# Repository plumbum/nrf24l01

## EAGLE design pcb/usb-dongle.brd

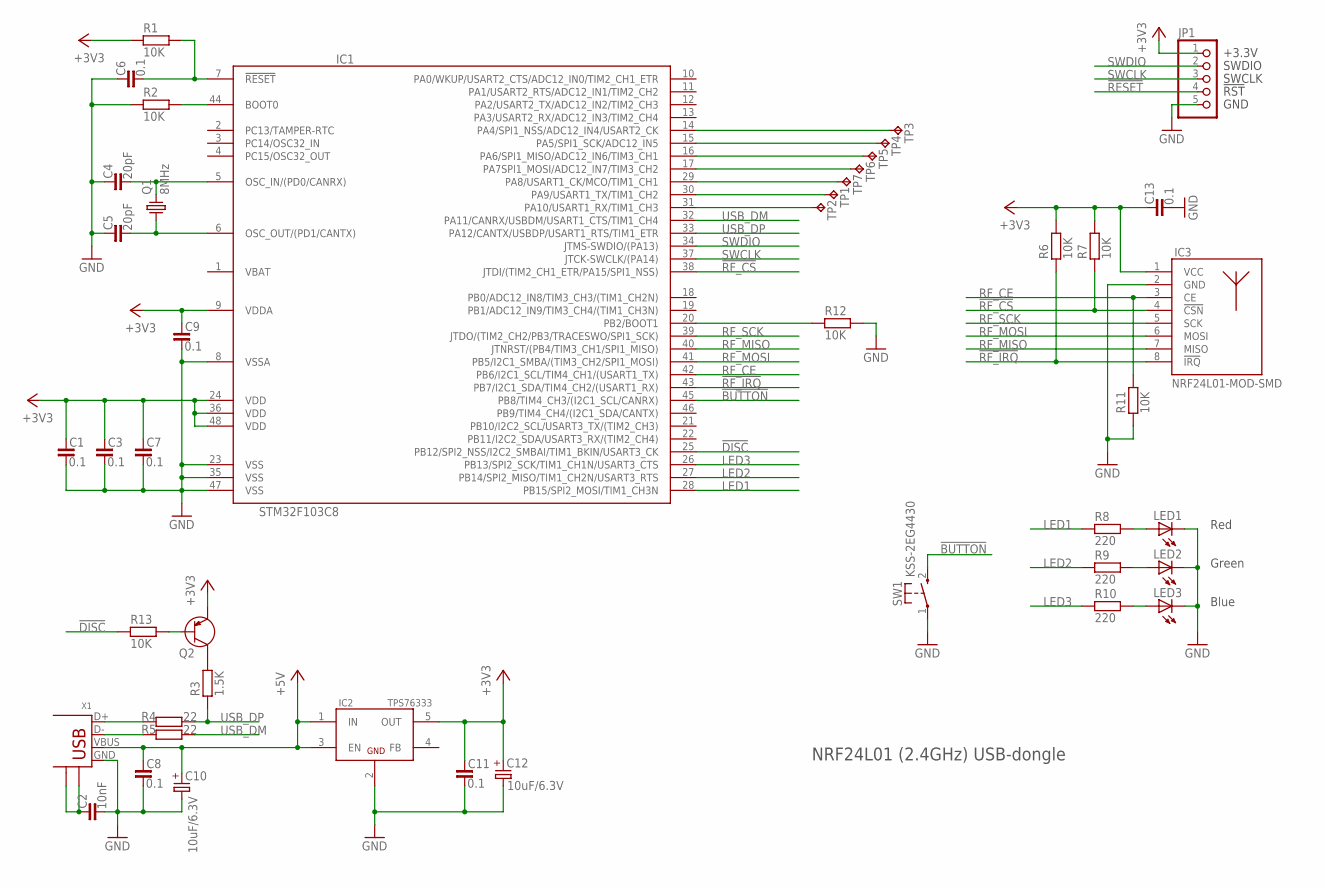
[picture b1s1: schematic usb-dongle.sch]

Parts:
C1, C3, C6, C7, C8, C9, C11, C13: 0.1; C0603
C2: 10nF; C1206
C4, C5: 20pF; C0603
C10, C12: 10uF/6.3V; SMC_B
IC1: STM32F103C8; LQFP48
IC2: TPS76333; SOT23-5
IC3: NRF24L01-MOD-SMD; SMD8-MODULE
JP1: SWD-5_2.00; 1X05M
LED1, LED2, LED3: LEDCHIPLED_0805; CHIPLED_0805
Q1: 8MHz; HC49/S
Q2: PNP-SOT23; SOT23
R1, R2, R6, R7, R11, R12, R13: 10K; R0603
R3: 1.5K; R0603
R4, R5: 22; R0603
R8, R9, R10: 220; R0603
SW1: KSS-2EG4430
TP1, TP2, TP3, TP4, TP5, TP6, TP7: TPB1,27; B1,27
X1: USB-MALE-A-H; USB-A-MH

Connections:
!BUTTON: IC1.45 (PB8/TIM4_CH3/(I2C1_SCL/CANRX)), SW1.2 (S)
!DISC: IC1.25 (PB12/SPI2_NSS/I2C2_SMBAI/TIM1_BKIN/USAR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), R13.1
!RESET: C6.2, IC1.7 (!RESET), JP1.4, R1.2
!RF_CS: IC1.38 (JTDI/(TIM2_CH1_ETR/PA15/SPI1_NSS)), IC3.4 (!CSN), R7.1
!RF_IRQ: IC1.43 (PB7/I2C1_SDA/TIM4_CH2/(USART1_RX)), IC3.8 (!IRQ), R6.1
+3V3: C1.1, C3.1, C7.1, C9.1, C11.1, C12.+, C13.1, IC1.9 (VDDA), IC1.24 (VDD), IC1.36 (VDD), IC1.48 (VDD), IC2.5 (OUT), IC3.1 (VCC), JP1.1, Q2.2 (E), R1.1, R6.2, R7.2
+5V: C8.1, C10.+, IC2.1 (IN), IC2.3 (EN), X1.VBUS
GND: C1.2, C2.2, C3.2, C4.1, C5.1, C6.1, C7.2, C8.2, C9.2, C10.-, C11.2, C12.-, C13.2, IC1.8 (VSSA), IC1.23 (VSS), IC1.35 (VSS), IC1.47 (VSS), IC2.2 (GND), IC3.2 (GND), JP1.5, LED1.C, LED2.C, LED3.C, R2.1, R11.1, R12.2, SW1.1, X1.GND
LED1: IC1.28 (PB15/SPI2_MOSI/TIM1_CH3N), R8.1
LED2: IC1.27 (PB14/SPI2_MISO/TIM1_CH2N/USART3_RTS), R9.1
LED3: IC1.26 (PB13/SPI2_SCK/TIM1_CH1N/USART3_CTS), R10.1
unnamed: C2.1, X1.P$5, X1.P$6
unnamed: R4.1, X1.D+
unnamed: R5.1, X1.D-
unnamed: IC1.30 (PA9/USART1_TX/TIM1_CH2), TP1.PP
unnamed: IC1.31 (PA10/USART1_RX/TIM1_CH3), TP2.PP
unnamed: C4.2, IC1.5 (OSC_IN/(PD0/CANRX)), Q1.2
unnamed: C5.2, IC1.6 (OSC_OUT/(PD1/CANTX)), Q1.1
unnamed: LED1.A, R8.2
unnamed: LED2.A, R9.2
unnamed: LED3.A, R10.2
unnamed: IC1.44 (BOOT0), R2.2
unnamed: IC1.14 (PA4/SPI1_NSS/ADC12_IN4/USART2_CK), TP3.PP
unnamed: IC1.15 (PA5/SPI1_SCK/ADC12_IN5), TP4.PP
unnamed: IC1.16 (PA6/SPI1_MISO/ADC12_IN6/TIM3_CH1), TP5.PP
unnamed: IC1.17 (PA7SPI1_MOSI/ADC12_IN7/TIM3_CH2), TP6.PP
unnamed: IC1.29 (PA8/USART1_CK/MCO/TIM1_CH1), TP7.PP
unnamed: IC1.20 (PB2/BOOT1), R12.1
unnamed: Q2.1 (B), R13.2
unnamed: Q2.3 (C), R3.2
RF_CE: IC1.42 (PB6/I2C1_SCL/TIM4_CH1/(USART1_TX)), IC3.3 (CE), R11.2
RF_MISO: IC1.40 (JTNRST/(PB4/TIM3_CH1/SPI1_MISO)), IC3.7 (MISO)
RF_MOSI: IC1.41 (PB5/I2C1_SMBA/(TIM3_CH2/SPI1_MOSI)), IC3.6 (MOSI)
RF_SCK: IC1.39 (JTDO/(TIM2_CH2/PB3/TRACESWO/SPI1_SCK)), IC3.5 (SCK)
SWCLK: IC1.37 (JTCK-SWCLK/(PA14)), JP1.3
SWDIO: IC1.34 (JTMS-SWDIO/(PA13)), JP1.2
USB_DM: IC1.32 (PA11/CANRX/USBDM/USART1_CTS/TIM1_CH4), R5.2
USB_DP: IC1.33 (PA12/CANTX/USBDP/USART1_RTS/TIM1_ETR), R3.1, R4.2
VBAT: IC1.1 (VBAT)

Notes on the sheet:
Red
Green
Blue
NRF24L01 (2.4GHz) USB-dongle

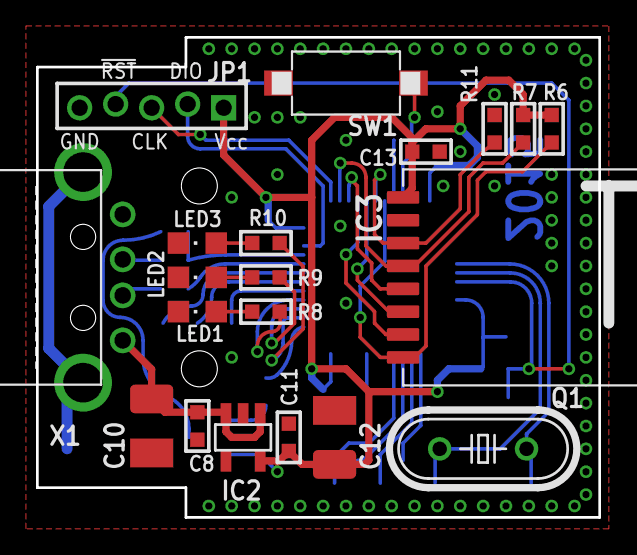
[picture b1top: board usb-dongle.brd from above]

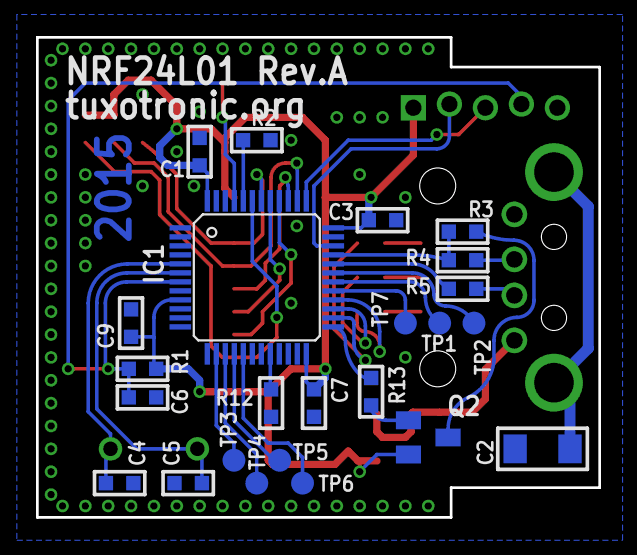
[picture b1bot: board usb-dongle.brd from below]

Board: 2 copper layers, 31.2 x 26.7 mm, 44 parts (24 on the bottom side), 38 nets.

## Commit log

2015-04-22 USB-dongle in progress
2015-04-23 USB-dongle. need review

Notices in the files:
parts and their libraries:
vreg-linear: 2009 Draw by Ivan A-R. License CC-BY-SA 3.0
